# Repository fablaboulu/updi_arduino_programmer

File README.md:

# Description
This board is a updi programmer that utilizes Arduino IDE to program AVR microcontroller.

# Instructions
* Use the Eagle files included in order to create the board to mill. In addition, the '.png' files to be used with [mods](http://mods.cba.mit.edu/) are included.
 
## Files
* [Eagle Board file](updi_programmer.brd)
* [Eagle Schematics file](updi_programmer.sch)
* [Components](updi_programmer_components.jpg)
* [Interior](updi_programmer_outline.png)
* [Traces](updi_programmer_traces.png)
* [Calibration](updi_programmer_calib.png)
## Milling
For milling we use a Roland SRM-20 with a 0.2-0.5 mm V-milling bit. The (updi_programmer_calib)[calibration file] was used for calibrating the milling depth to reach the correct milling width with a V-shape milling bit. 

When calculating the toolpaths with [mods](http://mods.cba.mit.edu/) We used 0.23 mm as the tool width for traces and calibration and 1 mm for the outline.

## Board dimensions:
*dpi*: 2400

*px*: 5932 x 2575

*mm*: 62.780 x 27.252

*in*: 2.472 x 1.073

# Links
* We followed the tutorials found at in:
  * [https://github.com/SpenceKonde/megaTinyCore/blob/master/MakeUPDIProgrammer.md](https://github.com/SpenceKonde/megaTinyCore/blob/master/MakeUPDIProgrammer.md)
  * [https://www.pcbway.com/project/shareproject/A_USB_stick_sized_UPDI_programmer.html](https://www.pcbway.com/project/shareproject/A_USB_stick_sized_UPDI_programmer.html)
  * [https://github.com/ElTangas/jtag2updi](https://github.com/ElTangas/jtag2updi)
  * [https://www.electronics-lab.com/project/getting-started-with-the-new-attiny-chips-programming-the-microchips-0-series-and-1-series-attiny-with-the-arduino-ide/](https://www.electronics-lab.com/project/getting-started-with-the-new-attiny-chips-programming-the-microchips-0-series-and-1-series-attiny-with-the-arduino-ide/)

# Authors
* Antti Mäntyniemi: antti.mantyniemi@oulu.fi

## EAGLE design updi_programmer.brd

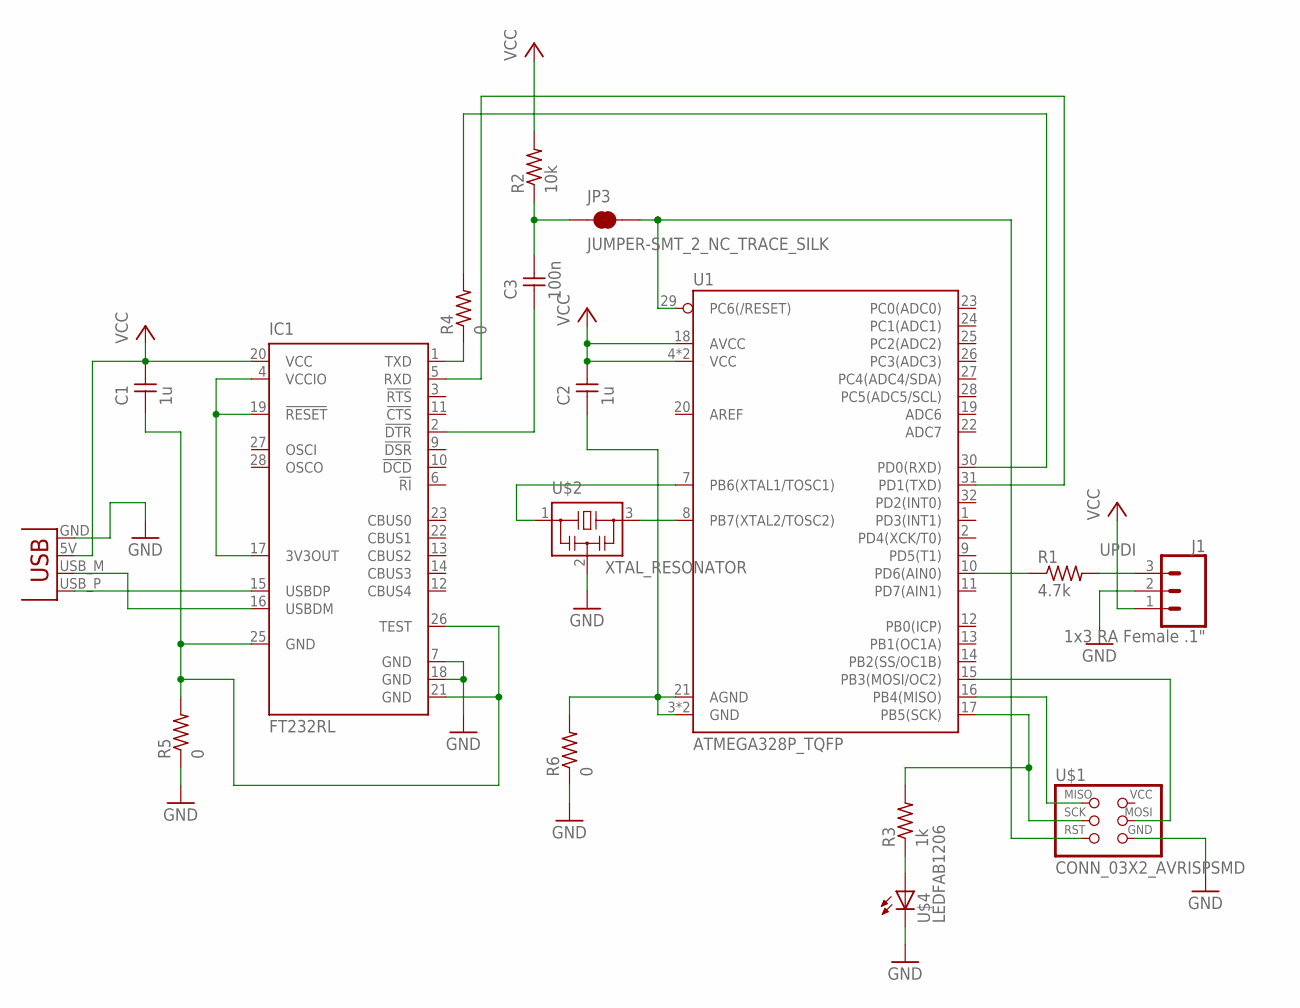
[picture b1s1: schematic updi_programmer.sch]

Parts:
C1, C2: 1u; C1206FAB
C3: 100n; C1206FAB
IC1: FT232RL; SSOP28
J1: 1x3 RA Female .1"; 1X03_SMD_RA_FEMALE
JP3: JUMPER-SMT_2_NC_TRACE_SILK; SMT-JUMPER_2_NC_TRACE_SILK
R1: 4.7k; R1206FAB
R2: 10k; R1206FAB
R3: 1k; R1206FAB
R4, R5, R6: 0; R1206FAB
U1: ATMEGA328P_TQFP; TQFP32-08
U$1: CONN_03X2_AVRISPSMD; 2X03SMD
U$2: XTAL_RESONATOR; EFOBM
U$4: LEDFAB1206; LED1206FAB
X1: CONN_USBPCB; USB-A-PCB

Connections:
GND: IC1.7 (GND), IC1.18 (GND), J1.2, R5.1, R6.1, U$1.6 (GND), U$2.2, U$4.2 (C), X1.GND
unnamed: IC1.1 (TXD), R4.1
unnamed: IC1.4 (VCCIO), IC1.17 (3V3OUT), IC1.19 (!RESET)
unnamed: IC1.15 (USBDP), X1.USB_P (D+)
unnamed: IC1.16 (USBDM), X1.USB_M (D-)
unnamed: U1.8 (PB7(XTAL2/TOSC2)), U$2.3
unnamed: U1.7 (PB6(XTAL1/TOSC1)), U$2.1
unnamed: R3.1, U$4.1 (A)
unnamed: C3.2, JP3.1, R2.1
unnamed: U1.16 (PB4(MISO)), U$1.1 (MISO)
unnamed: R1.1, U1.10 (PD6(AIN0))
unnamed: R3.2, U1.17 (PB5(SCK)), U$1.3 (SCK)
unnamed: U1.15 (PB3(MOSI/OC2)), U$1.4 (MOSI)
unnamed: JP3.2, U1.29 (PC6(/RESET)), U$1.5 (RST)
unnamed: C3.1, IC1.2 (!DTR)
unnamed: R4.2, U1.30 (PD0(RXD))
unnamed: IC1.5 (RXD), U1.31 (PD1(TXD))
unnamed: C2.1, R6.2, U1.3 (GND), U1.5 (GND), U1.21 (AGND)
unnamed: C1.1, IC1.21 (GND), IC1.25 (GND), IC1.26 (TEST), R5.2
UPDI: J1.3, R1.2
VCC: C1.2, C2.2, IC1.20 (VCC), J1.1, R2.2, U1.4 (VCC), U1.6 (VCC), U1.18 (AVCC), X1.5V (VBUS)

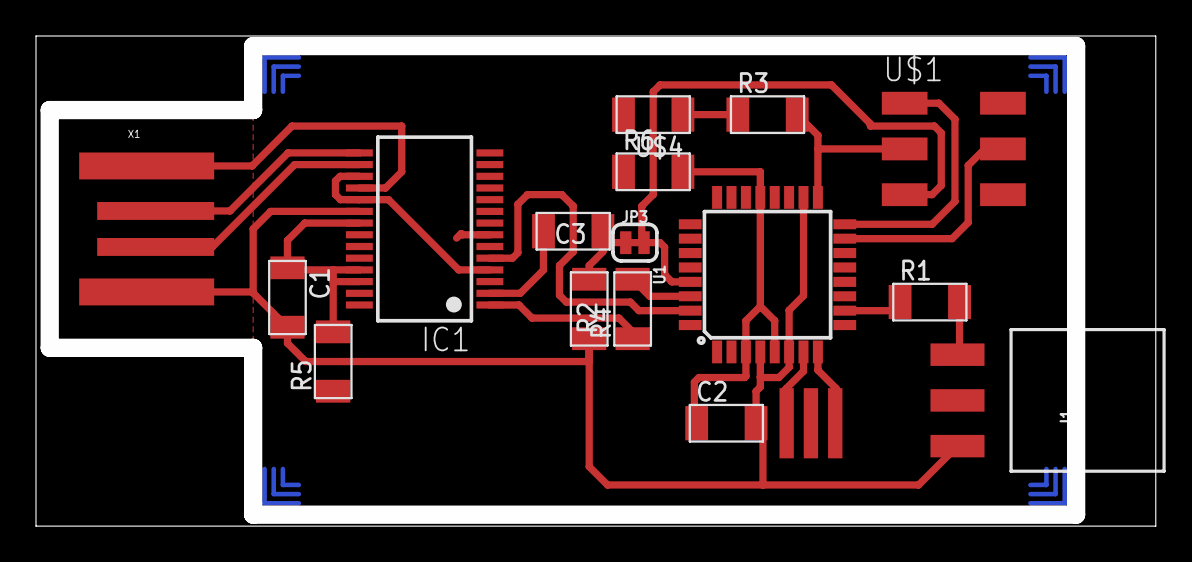
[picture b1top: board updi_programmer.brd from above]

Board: 2 copper layers, 61.2 x 26.2 mm, 17 parts (0 on the bottom side), 21 nets.

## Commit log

2020-02-19 Solved links syntax
    Modified links syntax
2020-02-19 Added images and corrected syntax

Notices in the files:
parts and their libraries:
SparkFun-IC-Microcontroller: Licensing: Creative Commons ShareAlike 4.0 International - https://creativecommons.org/licenses/by-sa/4.0
